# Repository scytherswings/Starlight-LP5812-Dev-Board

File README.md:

# Starlight-LP5812-Dev-Board
This is a dev board for the Texas Instruments LP5812 series ICs which can autonomously drive LEDs without an MCU

The intent of the project is to make it simple to start experimenting with the LP58XX series of chips from TI which offer some
interesting options for offloading LED animations from your MCU.

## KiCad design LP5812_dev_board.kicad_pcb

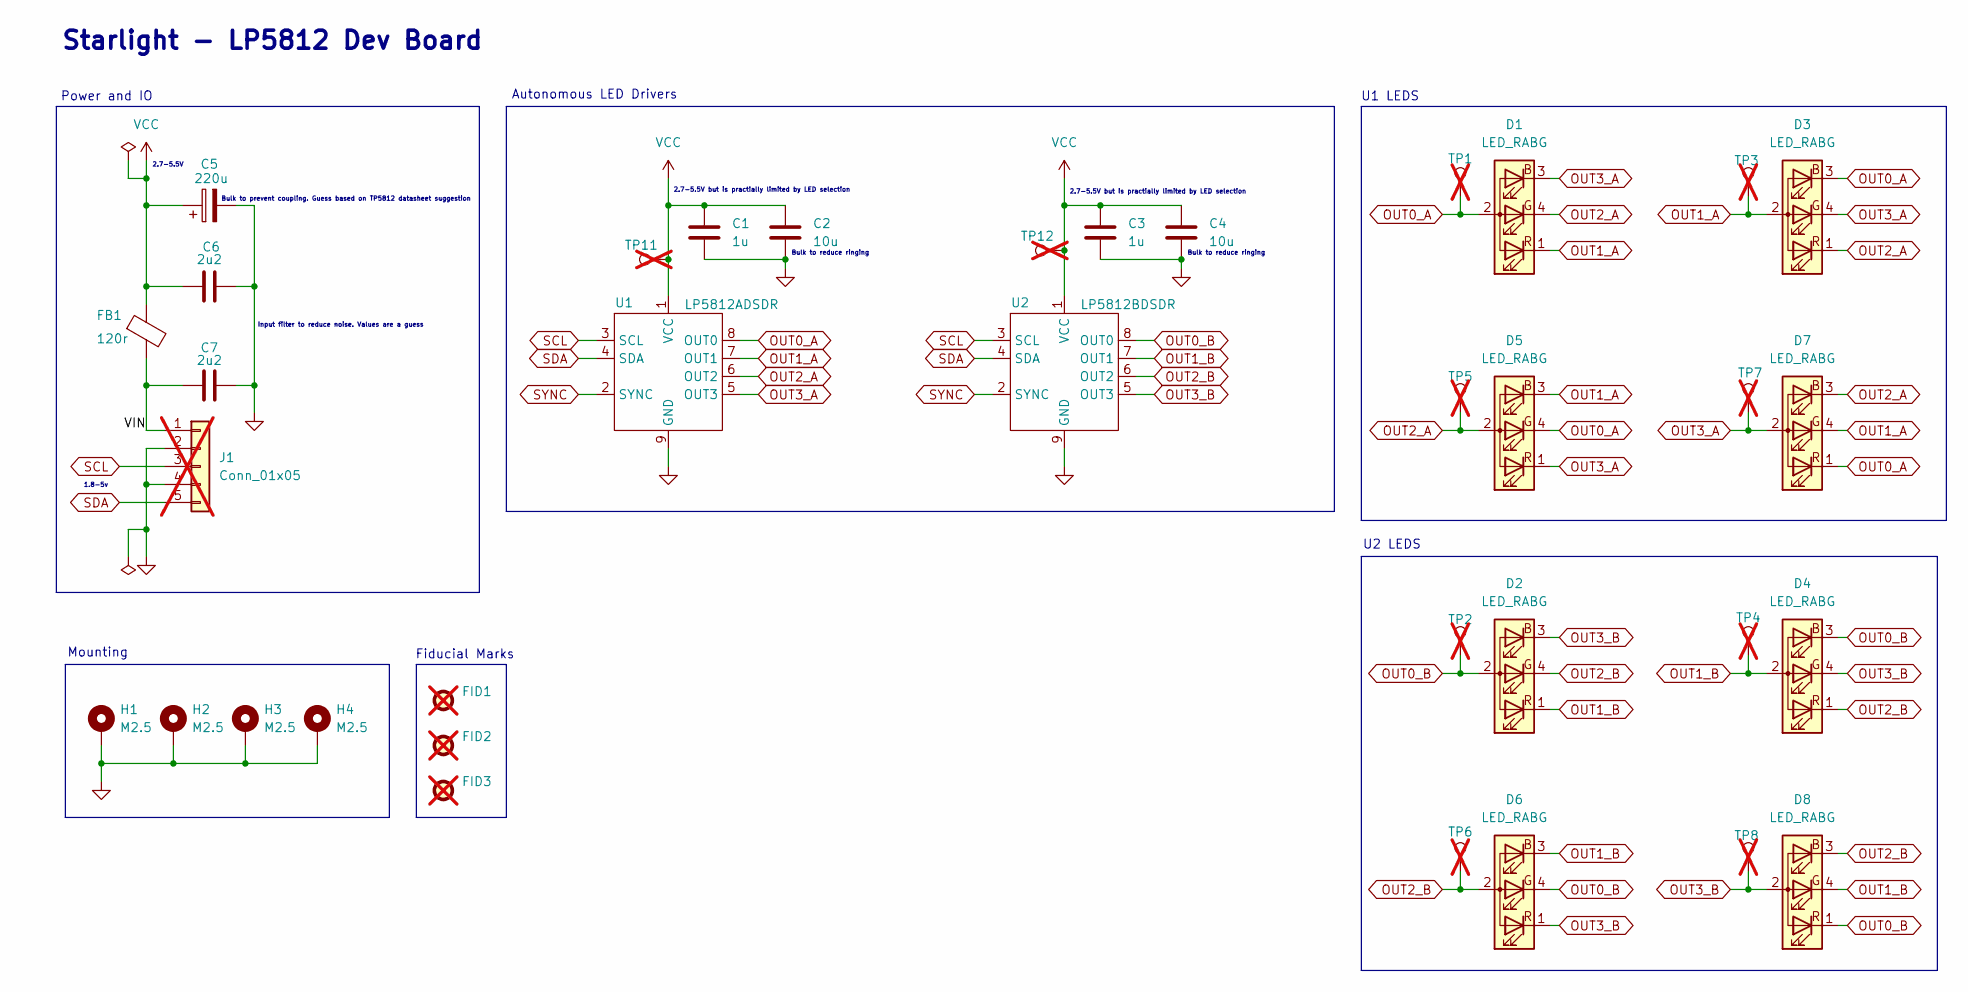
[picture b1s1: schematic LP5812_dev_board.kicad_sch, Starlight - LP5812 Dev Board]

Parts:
C1, C3: 1u; C_0603_1608Metric
C2, C4: 10u; C_0805_2012Metric
C5: 220u; C_Elec_6.3x7.7
C6, C7: 2u2; C_0603_1608Metric
D1, D2, D3, D4, D5, D6, D7, D8: LED_RABG; CLVBAFKACAEDH8BBB7A363
FB1: 120r; L_0603_1608Metric
FID1, FID2, FID3: Fiducial_1mm_Mask3mm; not fitted
H1, H2, H3, H4: M2.5; MountingHole_2.7mm_M2.5_Pad
J1: Conn_01x05; PinHeader_1x05_P2.54mm_Vertical; not fitted
TP1, TP2, TP3, TP4, TP5, TP6, TP7, TP8, TP11, TP12: TestPoint_Pad_D1.5mm; not fitted
U1: LP5812ADSDR
U2: LP5812BDSDR; LP5812ADSDR

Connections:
/VIN: C7.1, FB1.2, J1.1
GND: C1.2, C2.2, C3.2, C4.2, C5.2, C6.2, C7.2, H1.1, H2.1, H3.1, H4.1, J1.2, J1.4, U1.9 (GND), U2.9 (GND)
OUT0_A: D1.2 (A), D3.3 (BK), D5.4 (GK), D7.1 (RK), TP1.1, U1.8 (OUT0)
OUT0_B: D2.2 (A), D4.3 (BK), D6.4 (GK), D8.1 (RK), TP2.1, U2.8 (OUT0)
OUT1_A: D1.1 (RK), D3.2 (A), D5.3 (BK), D7.4 (GK), TP3.1, U1.7 (OUT1)
OUT1_B: D2.1 (RK), D4.2 (A), D6.3 (BK), D8.4 (GK), TP4.1, U2.7 (OUT1)
OUT2_A: D1.4 (GK), D3.1 (RK), D5.2 (A), D7.3 (BK), TP5.1, U1.6 (OUT2)
OUT2_B: D2.4 (GK), D4.1 (RK), D6.2 (A), D8.3 (BK), TP6.1, U2.6 (OUT2)
OUT3_A: D1.3 (BK), D3.4 (GK), D5.1 (RK), D7.2 (A), TP7.1, U1.5 (OUT3)
OUT3_B: D2.3 (BK), D4.4 (GK), D6.1 (RK), D8.2 (A), TP8.1, U2.5 (OUT3)
SCL: J1.3, U1.3 (SCL), U2.3 (SCL)
SDA: J1.5, U1.4 (SDA), U2.4 (SDA)
SYNC: U1.2 (SYNC), U2.2 (SYNC)
VCC: C1.1, C2.1, C3.1, C4.1, C5.1, C6.1, FB1.1, TP11.1, TP12.1, U1.1 (VCC), U2.1 (VCC)

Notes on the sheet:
Bulk to reduce ringing
Input filter to reduce noise. Values are a guess
Bulk to prevent coupling. Guess based on TP5812 datasheet suggestion
1.8-5v
Starlight - LP5812 Dev Board
Fiducial Marks
2.7-5.5V
U2 LEDS
Autonomous LED Drivers
Mounting
Power and IO
2.7-5.5V but is practially limited by LED selection
U1 LEDS

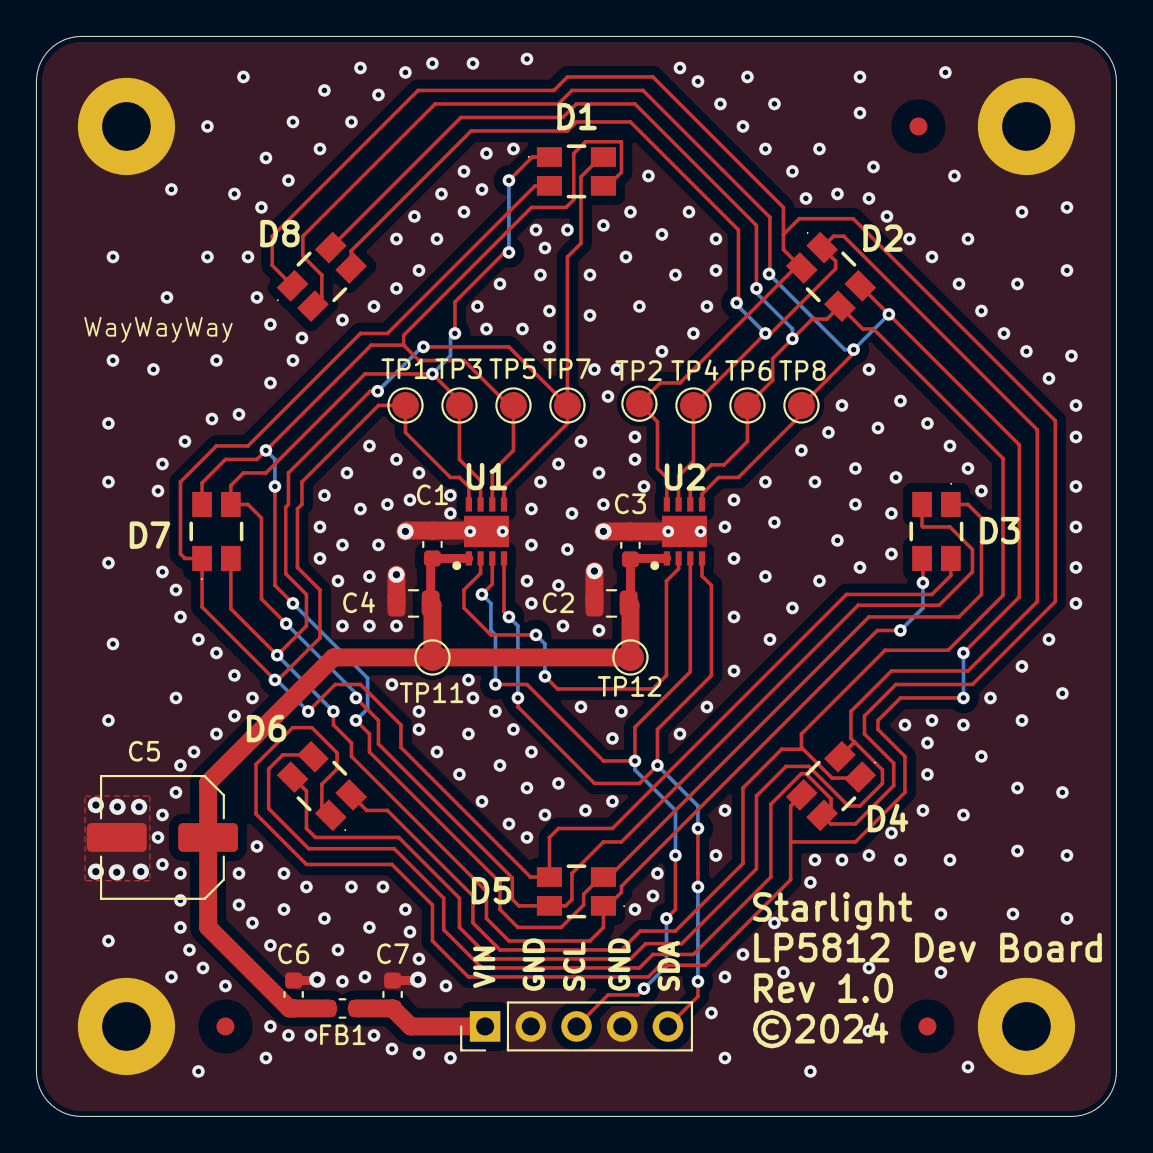
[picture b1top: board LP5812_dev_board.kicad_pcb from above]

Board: 2 copper layers, 60.0 x 60.0 mm, 36 parts (0 on the bottom side), 14 nets.

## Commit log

2024-03-20 Add lock file to gitignore
    Ignore log files
    Initial commit for version 1.0
    Name project
2024-03-20 gitignore
2024-03-21 Update LEDS for better reverse bias behavior and cost
2024-03-21 schematic plot and bom
2024-03-21 Update interactive bom
2024-03-21 Fix messed up annotations on LEDs
2024-03-22 Route PCB and generate outputs
2024-03-22 Mark header as DNP

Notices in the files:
LP5812_dev_board.kicad_pcb:
©2024
